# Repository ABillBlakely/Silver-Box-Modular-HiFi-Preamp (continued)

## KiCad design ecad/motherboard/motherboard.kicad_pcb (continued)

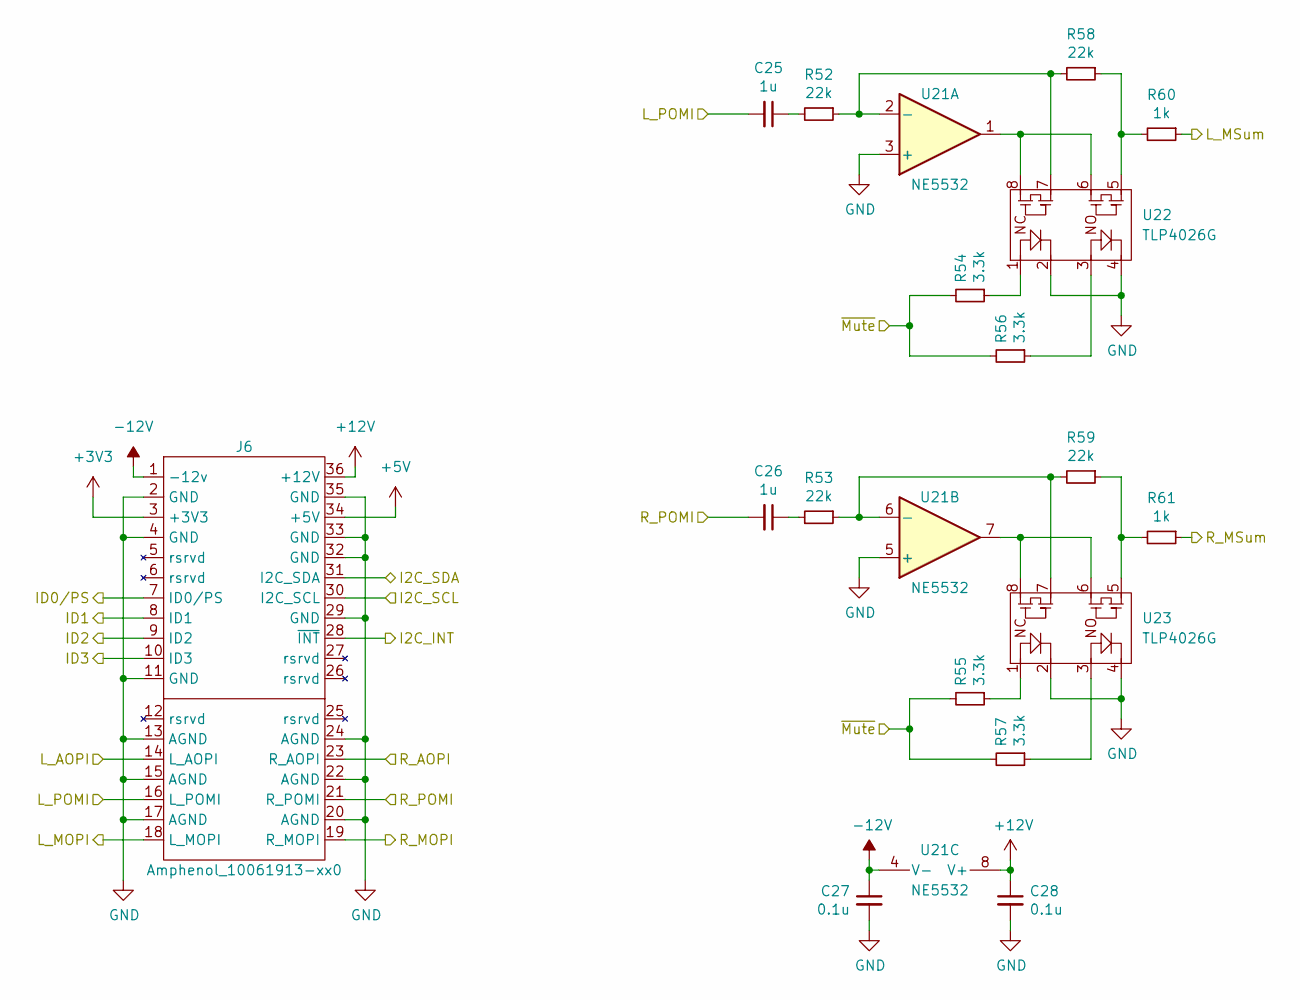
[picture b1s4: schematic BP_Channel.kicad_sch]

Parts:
C25, C26: 1u; C_2220_5650Metric_Pad1.97x5.40mm_HandSolder; MPN GRM55DR72E105KW01L
C27, C28: 0.1u; C_0603_1608Metric_Pad1.08x0.95mm_HandSolder; MPN C0603C104M5RACTU
J6: Amphenol_10061913-xx0; Card Edge Conn Amphenol 10061913-100PLF; MPN 10061913-110PLF
R52, R53, R58, R59: 22k; R_0603_1608Metric_Pad0.98x0.95mm_HandSolder; MPN RT0603FRE0722KL
R54, R55, R56, R57: 3.3k; R_0603_1608Metric_Pad0.98x0.95mm_HandSolder; MPN RC0603FR-073K3L
R60, R61: 1k; R_0603_1608Metric_Pad0.98x0.95mm_HandSolder; MPN RT0603FRE071KL
U21: NE5532; NE5532 SOIC8; MPN NE5532ADR
U22, U23: TLP4026G; MPN CPC2317NTR

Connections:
+3V3: J6.3 (+3V3); also elsewhere on the board
+5V: J6.34 (+5V); also elsewhere on the board
+12V: C28.1, J6.36 (+12V), U21.8 (V+); also elsewhere on the board
-12V: C27.1, J6.1 (-12v), U21.4 (V-); also elsewhere on the board
/BP_4Board_Control_and_Connect1/L_MSum: R60.1; also elsewhere on the board
/BP_4Board_Control_and_Connect1/L_POMI_4: J6.14 (L_AOPI); also elsewhere on the board
/BP_4Board_Control_and_Connect1/R_MSum: R61.1; also elsewhere on the board
/BP_4Board_Control_and_Connect1/R_POMI_4: J6.23 (R_AOPI); also elsewhere on the board
/BP_4Board_Control_and_Connect2/Channel1/I2C_INT: J6.28 (~INT); also elsewhere on the board
/BP_4Board_Control_and_Connect2/Channel1/I2C_SCL: J6.30 (I2C_SCL); also elsewhere on the board
/BP_4Board_Control_and_Connect2/Channel1/I2C_SDA: J6.31 (I2C_SDA); also elsewhere on the board
/BP_4Board_Control_and_Connect2/Channel1/ID0/PS: J6.7 (ID0/PS); also elsewhere on the board
/BP_4Board_Control_and_Connect2/Channel1/ID1: J6.8 (ID1); also elsewhere on the board
/BP_4Board_Control_and_Connect2/Channel1/ID2: J6.9 (ID2); also elsewhere on the board
/BP_4Board_Control_and_Connect2/Channel1/ID3: J6.10 (ID3); also elsewhere on the board
/BP_4Board_Control_and_Connect2/L_POMI_1: C25.2, J6.16 (L_POMI); also elsewhere on the board
/BP_4Board_Control_and_Connect2/R_POMI_1: C26.2, J6.21 (R_POMI); also elsewhere on the board
/L_MOPI: J6.18 (L_MOPI); also elsewhere on the board
/R_MOPI: J6.19 (R_MOPI); also elsewhere on the board
/~Mute_CH5: R54.2, R55.2, R56.2, R57.2; also elsewhere on the board
GND: C27.2, C28.2, J6.2 (GND), J6.4 (GND), J6.11 (GND), J6.13 (AGND), J6.15 (AGND), J6.17 (AGND), J6.20 (AGND), J6.22 (AGND), J6.24 (AGND), J6.29 (GND), J6.32 (GND), J6.33 (GND), J6.35 (GND), U21.3 (+), U21.5 (+), U22.2, U22.4, U23.2, U23.4; also elsewhere on the board
unnamed: C25.1, R52.2
unnamed: C26.1, R53.2
unnamed: R54.1, U22.1
unnamed: R55.1, U23.1
unnamed: R56.1, U22.3
unnamed: R57.1, U23.3
unnamed: R58.1, R60.2, U22.5
unnamed: R59.1, R61.2, U23.5
unnamed: U21.1, U22.6, U22.8
unnamed: U21.7, U23.6, U23.8
unnamed: R52.1, R58.2, U21.2 (-), U22.7
unnamed: R53.1, R59.2, U21.6 (-), U23.7

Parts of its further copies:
C6, C7, C10, C11, C14, C15, C18, C19, C29, C30, C33, C34, C37, C38: 1u; C_2220_5650Metric_Pad1.97x5.40mm_HandSolder; MPN GRM55DR72E105KW01L
C8, C9, C12, C13, C16, C17, C20, C21, C31, C32, C35, C36, C39, C40: 0.1u; C_0603_1608Metric_Pad1.08x0.95mm_HandSolder; MPN C0603C104M5RACTU
J2, J3, J4, J5, J7, J8, J9: Amphenol_10061913-xx0; Card Edge Conn Amphenol 10061913-100PLF; MPN 10061913-110PLF
R8, R9, R14, R15, R18, R19, R24, R25, R28, R29, R34, R35, R38, R39, R44, R45, R62, R63, R68, R69, R72, R73, R78, R79, R82, R83, R88, R89: 22k; R_0603_1608Metric_Pad0.98x0.95mm_HandSolder; MPN RT0603FRE0722KL
R10, R11, R12, R13, R20, R21, R22, R23, R30, R31, R32, R33, R40, R41, R42, R43, R64, R65, R66, R67, R74, R75, R76, R77, R84, R85, R86, R87: 3.3k; R_0603_1608Metric_Pad0.98x0.95mm_HandSolder; MPN RC0603FR-073K3L
R16, R17, R26, R27, R36, R37, R46, R47, R70, R71, R80, R81, R90, R91: 1k; R_0603_1608Metric_Pad0.98x0.95mm_HandSolder; MPN RT0603FRE071KL
U6, U9, U12, U15, U24, U27, U30: NE5532; NE5532 SOIC8; MPN NE5532ADR
U7, U8, U10, U11, U13, U14, U16, U17, U25, U26, U28, U29, U31, U32: TLP4026G; MPN CPC2317NTR

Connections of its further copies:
+3V3: J2.3 (+3V3), J3.3 (+3V3), J4.3 (+3V3), J5.3 (+3V3), J7.3 (+3V3), J8.3 (+3V3), J9.3 (+3V3); also elsewhere on the board
+5V: J2.34 (+5V), J3.34 (+5V), J4.34 (+5V), J5.34 (+5V), J7.34 (+5V), J8.34 (+5V), J9.34 (+5V); also elsewhere on the board
+12V: C9.1, C13.1, C17.1, C21.1, C32.1, C36.1, C40.1, J2.36 (+12V), J3.36 (+12V), J4.36 (+12V), J5.36 (+12V), J7.36 (+12V), J8.36 (+12V), J9.36 (+12V), U6.8 (V+), U9.8 (V+), U12.8 (V+), U15.8 (V+), U24.8 (V+), U27.8 (V+), U30.8 (V+); also elsewhere on the board
-12V: C8.1, C12.1, C16.1, C20.1, C31.1, C35.1, C39.1, J2.1 (-12v), J3.1 (-12v), J4.1 (-12v), J5.1 (-12v), J7.1 (-12v), J8.1 (-12v), J9.1 (-12v), U6.4 (V-), U9.4 (V-), U12.4 (V-), U15.4 (V-), U24.4 (V-), U27.4 (V-), U30.4 (V-); also elsewhere on the board
/BP_4Board_Control_and_Connect1/Channel1/I2C_INT: J2.28 (~INT); also elsewhere on the board
/BP_4Board_Control_and_Connect1/Channel1/I2C_SCL: J2.30 (I2C_SCL); also elsewhere on the board
/BP_4Board_Control_and_Connect1/Channel1/I2C_SDA: J2.31 (I2C_SDA); also elsewhere on the board
/BP_4Board_Control_and_Connect1/Channel1/ID0/PS: J2.7 (ID0/PS); also elsewhere on the board
/BP_4Board_Control_and_Connect1/Channel1/ID1: J2.8 (ID1); also elsewhere on the board
/BP_4Board_Control_and_Connect1/Channel1/ID2: J2.9 (ID2); also elsewhere on the board
/BP_4Board_Control_and_Connect1/Channel1/ID3: J2.10 (ID3); also elsewhere on the board
/BP_4Board_Control_and_Connect1/Channel2/I2C_INT: J3.28 (~INT); also elsewhere on the board
/BP_4Board_Control_and_Connect1/Channel2/I2C_SCL: J3.30 (I2C_SCL); also elsewhere on the board
/BP_4Board_Control_and_Connect1/Channel2/I2C_SDA: J3.31 (I2C_SDA); also elsewhere on the board
/BP_4Board_Control_and_Connect1/Channel2/ID0/PS: J3.7 (ID0/PS); also elsewhere on the board
/BP_4Board_Control_and_Connect1/Channel2/ID1: J3.8 (ID1); also elsewhere on the board
/BP_4Board_Control_and_Connect1/Channel2/ID2: J3.9 (ID2); also elsewhere on the board
/BP_4Board_Control_and_Connect1/Channel2/ID3: J3.10 (ID3); also elsewhere on the board
/BP_4Board_Control_and_Connect1/Channel3/I2C_INT: J4.28 (~INT); also elsewhere on the board
/BP_4Board_Control_and_Connect1/Channel3/I2C_SCL: J4.30 (I2C_SCL); also elsewhere on the board
/BP_4Board_Control_and_Connect1/Channel3/I2C_SDA: J4.31 (I2C_SDA); also elsewhere on the board
/BP_4Board_Control_and_Connect1/Channel3/ID0/PS: J4.7 (ID0/PS); also elsewhere on the board
/BP_4Board_Control_and_Connect1/Channel3/ID1: J4.8 (ID1); also elsewhere on the board
/BP_4Board_Control_and_Connect1/Channel3/ID2: J4.9 (ID2); also elsewhere on the board
/BP_4Board_Control_and_Connect1/Channel3/ID3: J4.10 (ID3); also elsewhere on the board
/BP_4Board_Control_and_Connect1/Channel4/I2C_INT: J5.28 (~INT); also elsewhere on the board
/BP_4Board_Control_and_Connect1/Channel4/I2C_SCL: J5.30 (I2C_SCL); also elsewhere on the board
/BP_4Board_Control_and_Connect1/Channel4/I2C_SDA: J5.31 (I2C_SDA); also elsewhere on the board
/BP_4Board_Control_and_Connect1/Channel4/ID0/PS: J5.7 (ID0/PS); also elsewhere on the board
/BP_4Board_Control_and_Connect1/Channel4/ID1: J5.8 (ID1); also elsewhere on the board
/BP_4Board_Control_and_Connect1/Channel4/ID2: J5.9 (ID2); also elsewhere on the board
/BP_4Board_Control_and_Connect1/Channel4/ID3: J5.10 (ID3); also elsewhere on the board
/BP_4Board_Control_and_Connect1/L_AOPI_1: J2.14 (L_AOPI)
/BP_4Board_Control_and_Connect1/L_MSum: R16.1, R26.1, R36.1, R46.1, R70.1, R80.1, R90.1; also elsewhere on the board
/BP_4Board_Control_and_Connect1/L_POMI_1: C6.2, J2.16 (L_POMI), J3.14 (L_AOPI)
/BP_4Board_Control_and_Connect1/L_POMI_2: C10.2, J3.16 (L_POMI), J4.14 (L_AOPI)
/BP_4Board_Control_and_Connect1/L_POMI_3: C14.2, J4.16 (L_POMI), J5.14 (L_AOPI)
/BP_4Board_Control_and_Connect1/L_POMI_4: C18.2, J5.16 (L_POMI); also elsewhere on the board
/BP_4Board_Control_and_Connect1/R_AOPI_1: J2.23 (R_AOPI)
/BP_4Board_Control_and_Connect1/R_MSum: R17.1, R27.1, R37.1, R47.1, R71.1, R81.1, R91.1; also elsewhere on the board
/BP_4Board_Control_and_Connect1/R_POMI_1: C7.2, J2.21 (R_POMI), J3.23 (R_AOPI)
/BP_4Board_Control_and_Connect1/R_POMI_2: C11.2, J3.21 (R_POMI), J4.23 (R_AOPI)
/BP_4Board_Control_and_Connect1/R_POMI_3: C15.2, J4.21 (R_POMI), J5.23 (R_AOPI)
/BP_4Board_Control_and_Connect1/R_POMI_4: C19.2, J5.21 (R_POMI); also elsewhere on the board
/BP_4Board_Control_and_Connect2/Channel2/I2C_INT: J7.28 (~INT); also elsewhere on the board
/BP_4Board_Control_and_Connect2/Channel2/I2C_SCL: J7.30 (I2C_SCL); also elsewhere on the board
/BP_4Board_Control_and_Connect2/Channel2/I2C_SDA: J7.31 (I2C_SDA); also elsewhere on the board
/BP_4Board_Control_and_Connect2/Channel2/ID0/PS: J7.7 (ID0/PS); also elsewhere on the board
/BP_4Board_Control_and_Connect2/Channel2/ID1: J7.8 (ID1); also elsewhere on the board
/BP_4Board_Control_and_Connect2/Channel2/ID2: J7.9 (ID2); also elsewhere on the board
/BP_4Board_Control_and_Connect2/Channel2/ID3: J7.10 (ID3); also elsewhere on the board
/BP_4Board_Control_and_Connect2/Channel3/I2C_INT: J8.28 (~INT); also elsewhere on the board
/BP_4Board_Control_and_Connect2/Channel3/I2C_SCL: J8.30 (I2C_SCL); also elsewhere on the board
/BP_4Board_Control_and_Connect2/Channel3/I2C_SDA: J8.31 (I2C_SDA); also elsewhere on the board
/BP_4Board_Control_and_Connect2/Channel3/ID0/PS: J8.7 (ID0/PS); also elsewhere on the board
/BP_4Board_Control_and_Connect2/Channel3/ID1: J8.8 (ID1); also elsewhere on the board
/BP_4Board_Control_and_Connect2/Channel3/ID2: J8.9 (ID2); also elsewhere on the board
/BP_4Board_Control_and_Connect2/Channel3/ID3: J8.10 (ID3); also elsewhere on the board
/BP_4Board_Control_and_Connect2/Channel4/I2C_INT: J9.28 (~INT); also elsewhere on the board
/BP_4Board_Control_and_Connect2/Channel4/I2C_SCL: J9.30 (I2C_SCL); also elsewhere on the board
/BP_4Board_Control_and_Connect2/Channel4/I2C_SDA: J9.31 (I2C_SDA); also elsewhere on the board
/BP_4Board_Control_and_Connect2/Channel4/ID0/PS: J9.7 (ID0/PS); also elsewhere on the board
/BP_4Board_Control_and_Connect2/Channel4/ID1: J9.8 (ID1); also elsewhere on the board
/BP_4Board_Control_and_Connect2/Channel4/ID2: J9.9 (ID2); also elsewhere on the board
/BP_4Board_Control_and_Connect2/Channel4/ID3: J9.10 (ID3); also elsewhere on the board
/BP_4Board_Control_and_Connect2/L_POMI_1: J7.14 (L_AOPI); also elsewhere on the board
/BP_4Board_Control_and_Connect2/L_POMI_2: C29.2, J7.16 (L_POMI), J8.14 (L_AOPI)
/BP_4Board_Control_and_Connect2/L_POMI_3: C33.2, J8.16 (L_POMI), J9.14 (L_AOPI)
/BP_4Board_Control_and_Connect2/L_POMI_4: C37.2, J9.16 (L_POMI)
/BP_4Board_Control_and_Connect2/R_POMI_1: J7.23 (R_AOPI); also elsewhere on the board
/BP_4Board_Control_and_Connect2/R_POMI_2: C30.2, J7.21 (R_POMI), J8.23 (R_AOPI)
/BP_4Board_Control_and_Connect2/R_POMI_3: C34.2, J8.21 (R_POMI), J9.23 (R_AOPI)
/BP_4Board_Control_and_Connect2/R_POMI_4: C38.2, J9.21 (R_POMI)
/L_MOPI: J2.18 (L_MOPI), J3.18 (L_MOPI), J4.18 (L_MOPI), J5.18 (L_MOPI), J7.18 (L_MOPI), J8.18 (L_MOPI), J9.18 (L_MOPI); also elsewhere on the board
/R_MOPI: J2.19 (R_MOPI), J3.19 (R_MOPI), J4.19 (R_MOPI), J5.19 (R_MOPI), J7.19 (R_MOPI), J8.19 (R_MOPI), J9.19 (R_MOPI); also elsewhere on the board
/~Mute_CH1: R10.2, R11.2, R12.2, R13.2; also elsewhere on the board
/~Mute_CH2: R20.2, R21.2, R22.2, R23.2; also elsewhere on the board
/~Mute_CH3: R30.2, R31.2, R32.2, R33.2; also elsewhere on the board
/~Mute_CH4: R40.2, R41.2, R42.2, R43.2; also elsewhere on the board
/~Mute_CH6: R64.2, R65.2, R66.2, R67.2; also elsewhere on the board
/~Mute_CH7: R74.2, R75.2, R76.2, R77.2; also elsewhere on the board
/~Mute_CH8: R84.2, R85.2, R86.2, R87.2; also elsewhere on the board
GND: C8.2, C9.2, C12.2, C13.2, C16.2, C17.2, C20.2, C21.2, C31.2, C32.2, C35.2, C36.2, C39.2, C40.2, J2.2 (GND), J2.4 (GND), J2.11 (GND), J2.13 (AGND), J2.15 (AGND), J2.17 (AGND), J2.20 (AGND), J2.22 (AGND), J2.24 (AGND), J2.29 (GND), J2.32 (GND), J2.33 (GND), J2.35 (GND), J3.2 (GND), J3.4 (GND), J3.11 (GND), J3.13 (AGND), J3.15 (AGND), J3.17 (AGND), J3.20 (AGND), J3.22 (AGND), J3.24 (AGND), J3.29 (GND), J3.32 (GND), J3.33 (GND), J3.35 (GND), J4.2 (GND), J4.4 (GND), J4.11 (GND), J4.13 (AGND), J4.15 (AGND), J4.17 (AGND), J4.20 (AGND), J4.22 (AGND), J4.24 (AGND), J4.29 (GND), J4.32 (GND), J4.33 (GND), J4.35 (GND), J5.2 (GND), J5.4 (GND), J5.11 (GND), J5.13 (AGND), J5.15 (AGND), J5.17 (AGND), J5.20 (AGND), J5.22 (AGND), J5.24 (AGND), J5.29 (GND), J5.32 (GND), J5.33 (GND), J5.35 (GND), J7.2 (GND), J7.4 (GND), J7.11 (GND), J7.13 (AGND), J7.15 (AGND), J7.17 (AGND), J7.20 (AGND), J7.22 (AGND), J7.24 (AGND), J7.29 (GND), J7.32 (GND), J7.33 (GND), J7.35 (GND), J8.2 (GND), J8.4 (GND), J8.11 (GND), J8.13 (AGND), J8.15 (AGND), J8.17 (AGND), J8.20 (AGND), J8.22 (AGND), J8.24 (AGND), J8.29 (GND), J8.32 (GND), J8.33 (GND), J8.35 (GND), J9.2 (GND), J9.4 (GND), J9.11 (GND), J9.13 (AGND), J9.15 (AGND), J9.17 (AGND), J9.20 (AGND), J9.22 (AGND), J9.24 (AGND), J9.29 (GND), J9.32 (GND), J9.33 (GND), J9.35 (GND), U6.3 (+), U6.5 (+), U7.2, U7.4, U8.2, U8.4, U9.3 (+), U9.5 (+), U10.2, U10.4, U11.2, U11.4, U12.3 (+), U12.5 (+), U13.2, U13.4, U14.2, U14.4, U15.3 (+), U15.5 (+), U16.2, U16.4, U17.2, U17.4, U24.3 (+), U24.5 (+), U25.2, U25.4, U26.2, U26.4, U27.3 (+), U27.5 (+), U28.2, U28.4, U29.2, U29.4, U30.3 (+), U30.5 (+), U31.2, U31.4, U32.2, U32.4; also elsewhere on the board
unnamed: C6.1, R8.2
unnamed: C7.1, R9.2
unnamed: C10.1, R18.2
unnamed: C11.1, R19.2
unnamed: C14.1, R28.2
unnamed: C15.1, R29.2
unnamed: C18.1, R38.2
unnamed: C19.1, R39.2
unnamed: C29.1, R62.2
unnamed: C30.1, R63.2
unnamed: C33.1, R72.2
unnamed: C34.1, R73.2
unnamed: C37.1, R82.2
unnamed: C38.1, R83.2
unnamed: R10.1, U7.1
unnamed: R11.1, U8.1
unnamed: R12.1, U7.3
unnamed: R13.1, U8.3
unnamed: R14.1, R16.2, U7.5
unnamed: R15.1, R17.2, U8.5
unnamed: R20.1, U10.1
unnamed: R21.1, U11.1
unnamed: R22.1, U10.3
unnamed: R23.1, U11.3
unnamed: R24.1, R26.2, U10.5
unnamed: R25.1, R27.2, U11.5
unnamed: R30.1, U13.1
unnamed: R31.1, U14.1
unnamed: R32.1, U13.3
unnamed: R33.1, U14.3
unnamed: R34.1, R36.2, U13.5
unnamed: R35.1, R37.2, U14.5
unnamed: R40.1, U16.1
unnamed: R41.1, U17.1
unnamed: R42.1, U16.3
unnamed: R43.1, U17.3
unnamed: R44.1, R46.2, U16.5
unnamed: R45.1, R47.2, U17.5
unnamed: R64.1, U25.1
unnamed: R65.1, U26.1
unnamed: R66.1, U25.3
unnamed: R67.1, U26.3
unnamed: R68.1, R70.2, U25.5
unnamed: R69.1, R71.2, U26.5
unnamed: R74.1, U28.1
unnamed: R75.1, U29.1
unnamed: R76.1, U28.3
unnamed: R77.1, U29.3
unnamed: R78.1, R80.2, U28.5
unnamed: R79.1, R81.2, U29.5
unnamed: R84.1, U31.1
unnamed: R85.1, U32.1
unnamed: R86.1, U31.3
unnamed: R87.1, U32.3
unnamed: R88.1, R90.2, U31.5
unnamed: R89.1, R91.2, U32.5
unnamed: U6.1, U7.6, U7.8
unnamed: U6.7, U8.6, U8.8
unnamed: R8.1, R14.2, U6.2 (-), U7.7
unnamed: R9.1, R15.2, U6.6 (-), U8.7
unnamed: R18.1, R24.2, U9.2 (-), U10.7
unnamed: R19.1, R25.2, U9.6 (-), U11.7
unnamed: U9.1, U10.6, U10.8
unnamed: U9.7, U11.6, U11.8
unnamed: U12.1, U13.6, U13.8
unnamed: U12.7, U14.6, U14.8
unnamed: R28.1, R34.2, U12.2 (-), U13.7
unnamed: R29.1, R35.2, U12.6 (-), U14.7
unnamed: U15.1, U16.6, U16.8
unnamed: U15.7, U17.6, U17.8
unnamed: R38.1, R44.2, U15.2 (-), U16.7
unnamed: R39.1, R45.2, U15.6 (-), U17.7
unnamed: U24.1, U25.6, U25.8
unnamed: U24.7, U26.6, U26.8
unnamed: R62.1, R68.2, U24.2 (-), U25.7
unnamed: R63.1, R69.2, U24.6 (-), U26.7
unnamed: U27.1, U28.6, U28.8
unnamed: U27.7, U29.6, U29.8
unnamed: R72.1, R78.2, U27.2 (-), U28.7
unnamed: R73.1, R79.2, U27.6 (-), U29.7
unnamed: U30.1, U31.6, U31.8
unnamed: U30.7, U32.6, U32.8
unnamed: R82.1, R88.2, U30.2 (-), U31.7
unnamed: R83.1, R89.2, U30.6 (-), U32.7

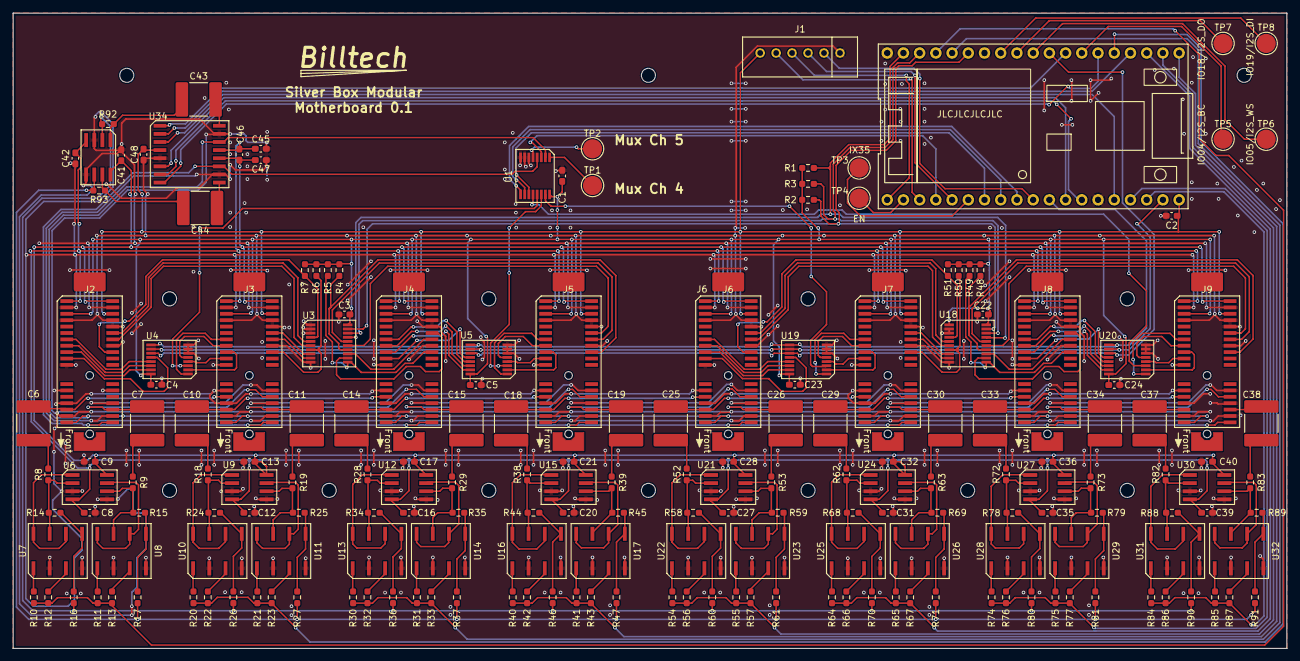
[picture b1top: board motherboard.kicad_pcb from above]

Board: 2 copper layers, 199.5 x 99.5 mm, 192 parts (0 on the bottom side), 221 nets.

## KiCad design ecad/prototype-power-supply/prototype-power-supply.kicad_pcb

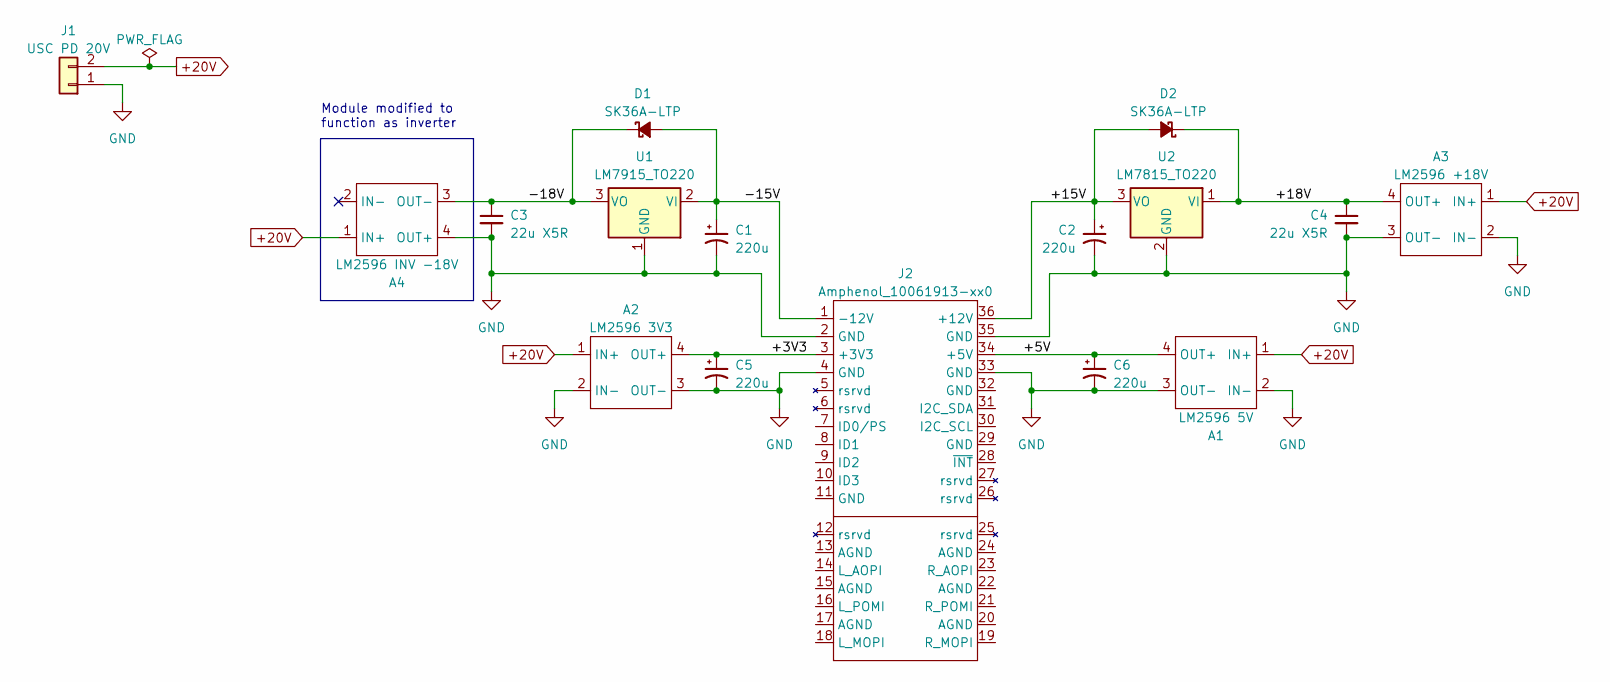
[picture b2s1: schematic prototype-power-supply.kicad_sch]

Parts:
A1: LM2596 5V; LM2596 module
A2: LM2596 3V3; LM2596 module
A3: LM2596 +18V; LM2596 module
A4: LM2596 INV -18V; LM2596 module
C1, C2, C5, C6: 220u; CP_Elec_12.5x13.5
C3, C4: 22u X5R; C_1210_3225Metric
D1, D2: SK36A-LTP; D_SMA_Handsoldering
J1: USC PD 20V; JST_XH_B2B-XH-A_1x02_P2.50mm_Vertical
J2: Amphenol_10061913-xx0; Card Edge board Amphenol 10061913-100PLF
U1: LM7915_TO220; TO-220-3_Vertical
U2: LM7815_TO220; TO-220-3_Vertical

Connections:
+20V: A1.1 (IN+), A2.1 (IN+), A3.1 (IN+), A4.1 (IN+), J1.2
/+3V3: A2.4 (OUT+), C5.1, J2.3 (+3V3)
/+5V: A1.4 (OUT+), C6.1, J2.34 (+5V)
/+15V: C2.1, D2.2 (A), J2.36 (+12V), U2.3 (VO)
/+18V: A3.4 (OUT+), C4.1, D2.1 (K), U2.1 (VI)
/-15V: C1.1, D1.2 (A), J2.1 (-12V), U1.2 (VI)
/-18V: A4.3 (OUT-), C3.1, D1.1 (K), U1.3 (VO)
GND: A1.2 (IN-), A1.3 (OUT-), A2.2 (IN-), A2.3 (OUT-), A3.2 (IN-), A3.3 (OUT-), A4.4 (OUT+), C1.2, C2.2, C3.2, C4.2, C5.2, C6.2, J1.1, J2.2 (GND), J2.4 (GND), J2.33 (GND), J2.35 (GND), U1.1 (GND), U2.2 (GND)

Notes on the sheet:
Module modified to function as inverter

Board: 2 copper layers, 16 parts (2 on the bottom side), 8 nets, no tracks yet.

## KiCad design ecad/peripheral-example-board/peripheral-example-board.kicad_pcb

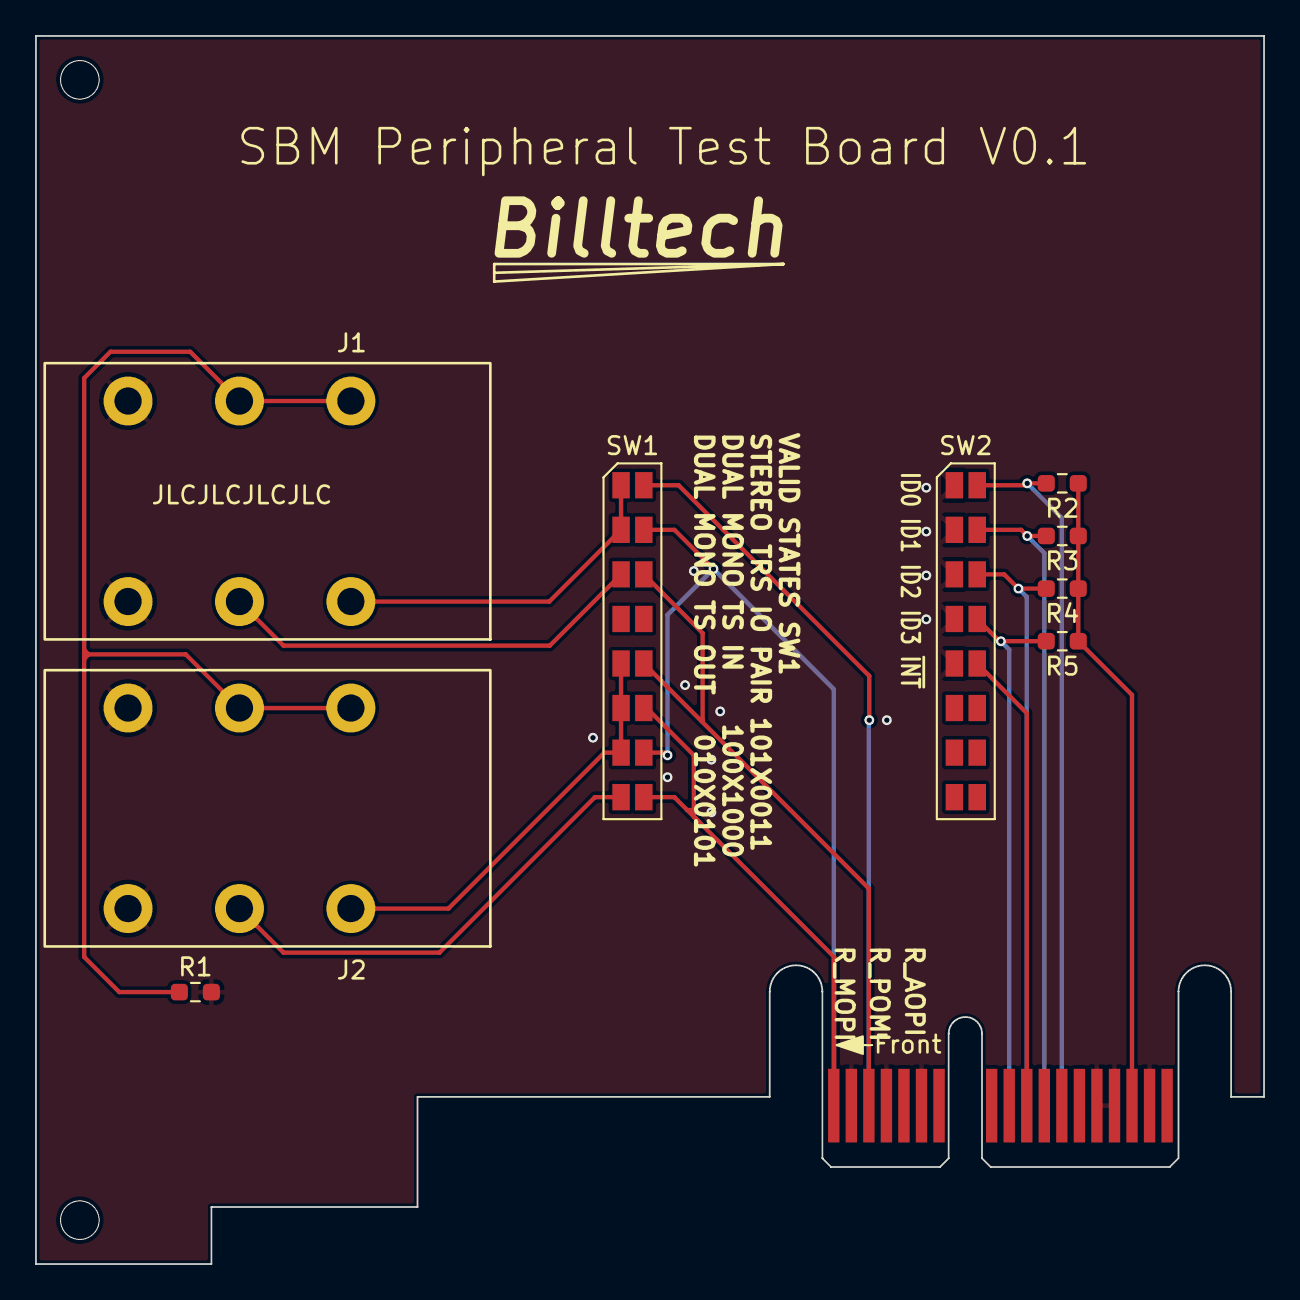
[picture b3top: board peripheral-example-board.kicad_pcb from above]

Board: 2 copper layers, 70.0 x 70.0 mm, 11 parts (0 on the bottom side), 16 nets.

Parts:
J1, J2: Amphenol_ACJS-MHOM; ACJS-MHOM
LOGO: Billtech
P1: Amphenol_10061913-xx0; Card Edge board Amphenol 10061913-100PLF
R1, R2, R3, R4, R5: 10k; R_0603_1608Metric_Pad0.98x0.95mm_HandSolder
SW1, SW2: SW_DIP_x08; 1x8 solder bridge 1x1.5x0.3

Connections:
/+5V: P1.34 (+5V), R2.1, R3.1, R4.1, R5.1
/ID0: P1.7 (ID0/PS), R2.2, SW2.16
/ID1: P1.8 (ID1), R3.2, SW2.15
/ID2: P1.9 (ID2), R4.2, SW2.14
/ID3: P1.10 (ID3), R5.2, SW2.13
/L_MOPI: P1.18 (L_MOPI), SW1.10, SW1.15
/L_POMI: P1.16 (L_POMI), SW1.16
/R1: J1.R, SW1.3
/R2: J2.R, SW1.8
/R_MOPI: P1.19 (R_MOPI), SW1.9, SW1.11
/R_POMI: P1.21 (R_POMI), SW1.12, SW1.14
/T1: J1.T, SW1.1, SW1.2
/T2: J2.T, SW1.5, SW1.6, SW1.7
/~INT: P1.28 (~INT), SW2.12
GND: J1.S, J1.SN, J2.S, J2.SN, P1.2 (GND), P1.4 (GND), P1.11 (GND), P1.13 (AGND), P1.15 (AGND), P1.17 (AGND), P1.20 (AGND), P1.22 (AGND), P1.24 (AGND), P1.29 (GND), P1.32 (GND), P1.33 (GND), P1.35 (GND), R1.2, SW2.1, SW2.2, SW2.3, SW2.4, SW2.5
unnamed: J1.RN, J1.TN, J2.RN, J2.TN, R1.1

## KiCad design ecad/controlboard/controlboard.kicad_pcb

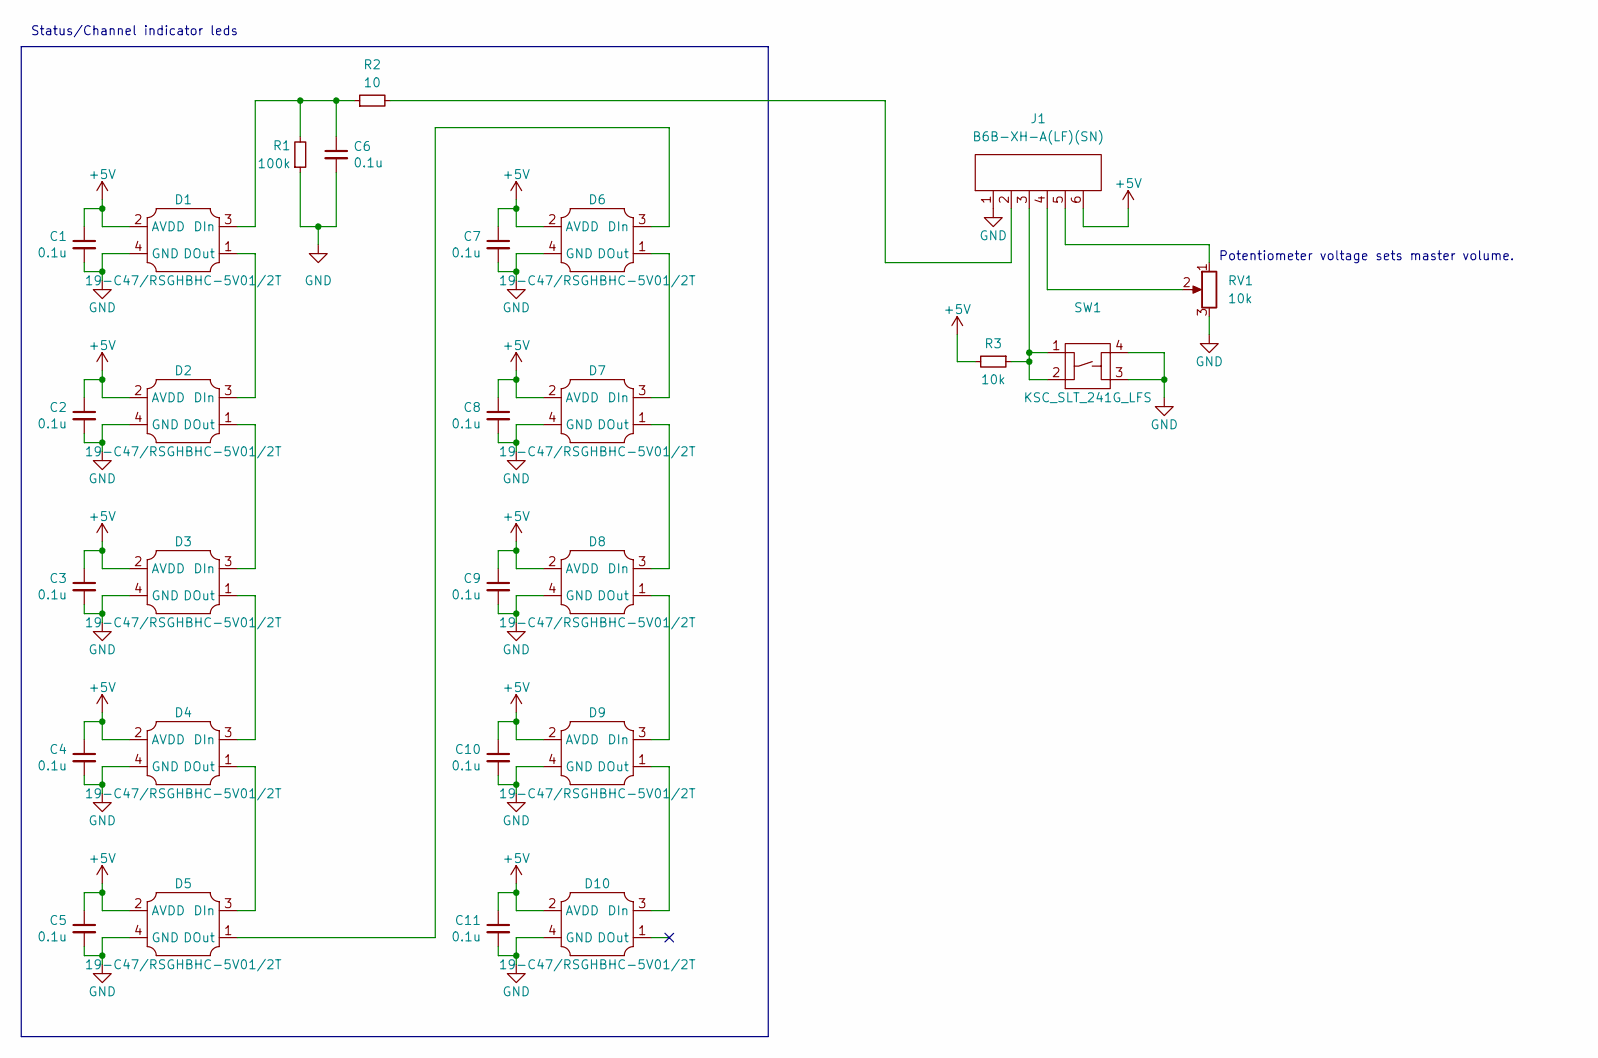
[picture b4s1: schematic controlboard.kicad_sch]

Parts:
C1, C2, C3, C4, C5, C6, C7, C8, C9, C10, C11: 0.1u; C_0603_1608Metric_Pad1.08x0.95mm_HandSolder
D1, D2, D3, D4, D5, D6, D7, D8, D9, D10: 19-C47/RSGHBHC-5V01/2T; 19-C47 RSGHBHC-5V01 2T
J1: B6B-XH-A(LF)(SN)
R1: 100k; R_0603_1608Metric_Pad0.98x0.95mm_HandSolder
R2: 10; R_0603_1608Metric_Pad0.98x0.95mm_HandSolder
R3: 10k; R_0603_1608Metric_Pad0.98x0.95mm_HandSolder
RV1: 10k; Bourns PTV11-4425A
SW1: KSC_SLT_241G_LFS; KSC SLT 241G LFS

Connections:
+5V: C1.1, C2.1, C3.1, C4.1, C5.1, C7.1, C8.1, C9.1, C10.1, C11.1, D1.2 (AVDD), D2.2 (AVDD), D3.2 (AVDD), D4.2 (AVDD), D5.2 (AVDD), D6.2 (AVDD), D7.2 (AVDD), D8.2 (AVDD), D9.2 (AVDD), D10.2 (AVDD), J1.6, R3.2
GND: C1.2, C2.2, C3.2, C4.2, C5.2, C6.2, C7.2, C8.2, C9.2, C10.2, C11.2, D1.4 (GND), D2.4 (GND), D3.4 (GND), D4.4 (GND), D5.4 (GND), D6.4 (GND), D7.4 (GND), D8.4 (GND), D9.4 (GND), D10.4 (GND), J1.1, R1.1, RV1.3, SW1.3, SW1.4
unnamed: C6.1, D1.3 (DIn), R1.2, R2.1
unnamed: D1.1 (DOut), D2.3 (DIn)
unnamed: D2.1 (DOut), D3.3 (DIn)
unnamed: D3.1 (DOut), D4.3 (DIn)
unnamed: D4.1 (DOut), D5.3 (DIn)
unnamed: D5.1 (DOut), D6.3 (DIn)
unnamed: D6.1 (DOut), D7.3 (DIn)
unnamed: D7.1 (DOut), D8.3 (DIn)
unnamed: D8.1 (DOut), D9.3 (DIn)
unnamed: D9.1 (DOut), D10.3 (DIn)
unnamed: J1.2, R2.2
unnamed: J1.3, R3.1, SW1.1, SW1.2
unnamed: J1.4, RV1.2
unnamed: J1.5, RV1.1

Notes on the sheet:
Status/Channel indicator leds
Potentiometer voltage sets master volume.

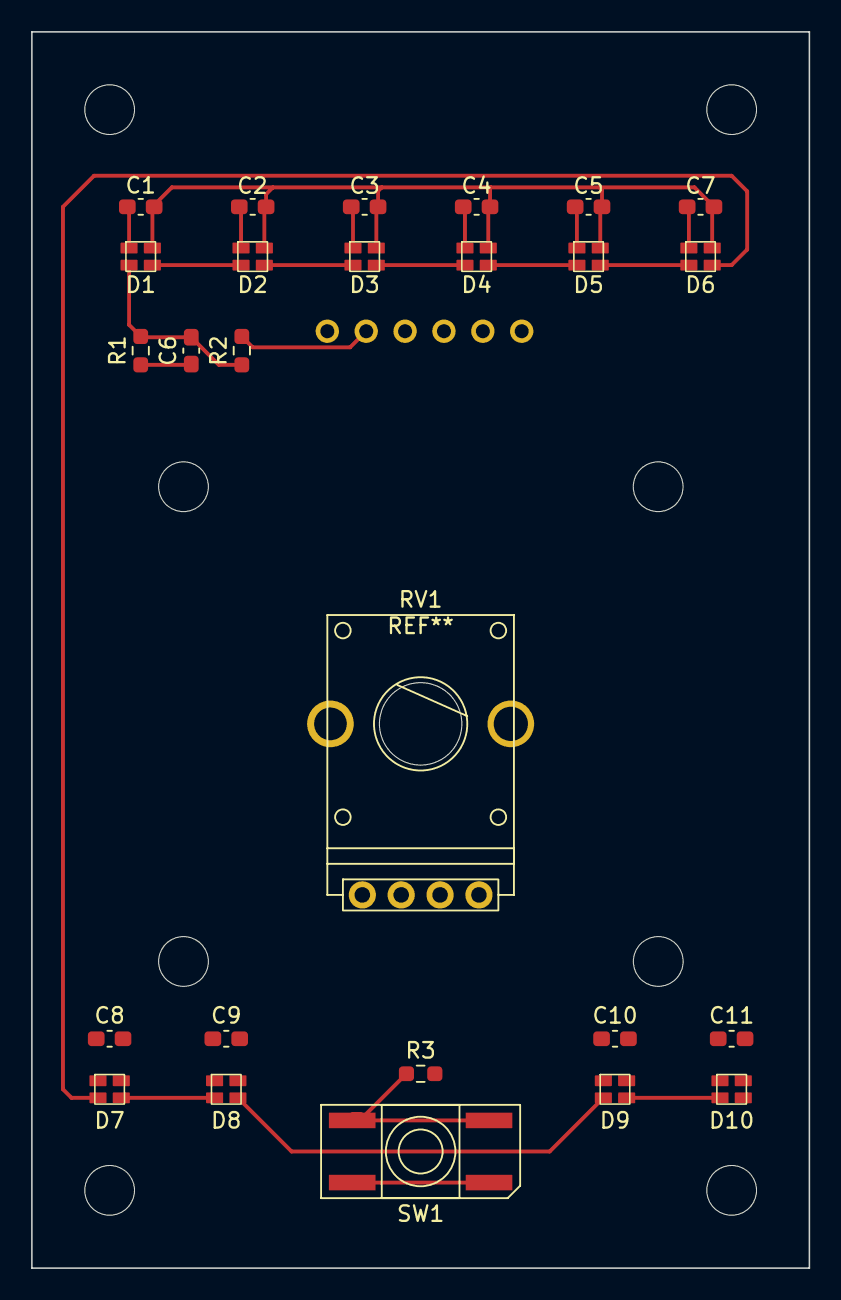
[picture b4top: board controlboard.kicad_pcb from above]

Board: 2 copper layers, 50.0 x 79.5 mm, 27 parts (1 on the bottom side), 16 nets.

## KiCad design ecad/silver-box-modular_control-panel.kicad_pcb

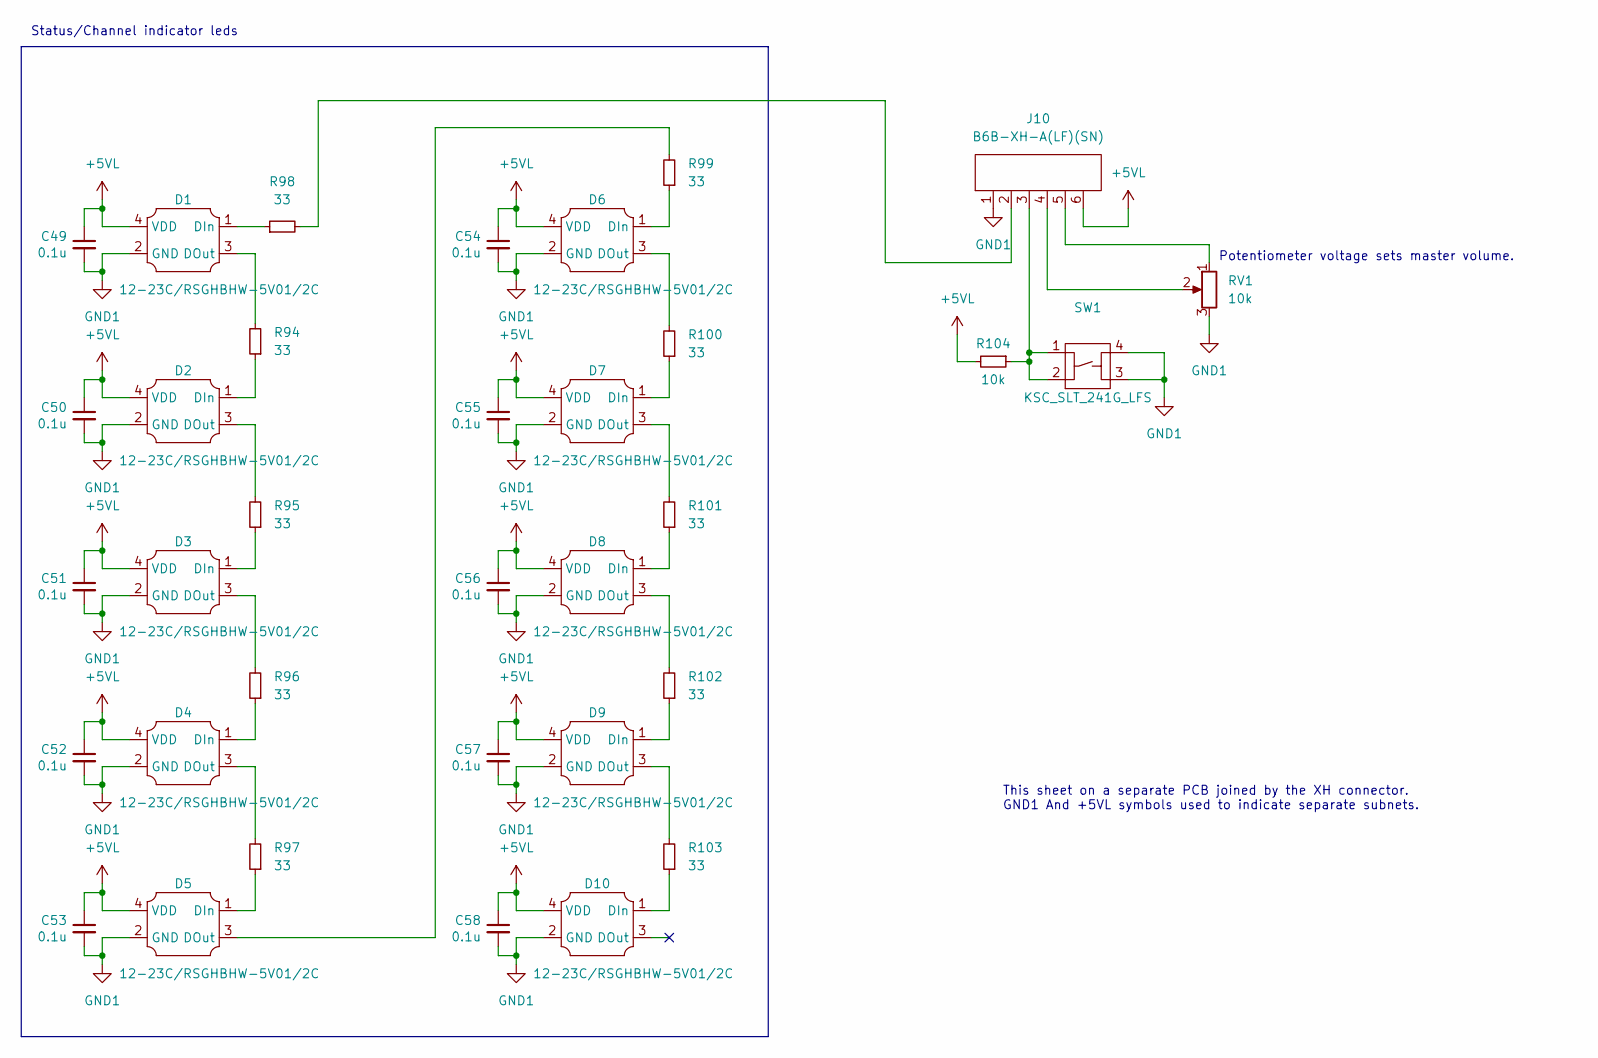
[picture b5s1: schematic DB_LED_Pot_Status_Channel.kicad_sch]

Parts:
C49, C50, C51, C52, C53, C54, C55, C56, C57, C58: 0.1u; C_0603_1608Metric_Pad1.08x0.95mm_HandSolder
D1, D2, D3, D4, D5, D6, D7, D8, D9, D10: 12-23C/RSGHBHW-5V01/2C; 12-23C-RSGHBHW-5V01-2C
J10: B6B-XH-A(LF)(SN)
R94, R95, R96, R97, R98, R99, R100, R101, R102, R103: 33; R_0603_1608Metric_Pad0.98x0.95mm_HandSolder
R104: 10k; R_0603_1608Metric_Pad0.98x0.95mm_HandSolder
RV1: 10k; Bourns PTV11-4425A
SW1: KSC_SLT_241G_LFS; KSC SLT 241G LFS

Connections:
+5VL: C49.1, C50.1, C51.1, C52.1, C53.1, C54.1, C55.1, C56.1, C57.1, C58.1, D1.4 (VDD), D2.4 (VDD), D3.4 (VDD), D4.4 (VDD), D5.4 (VDD), D6.4 (VDD), D7.4 (VDD), D8.4 (VDD), D9.4 (VDD), D10.4 (VDD), J10.6, R104.2
GND1: C49.2, C50.2, C51.2, C52.2, C53.2, C54.2, C55.2, C56.2, C57.2, C58.2, D1.2 (GND), D2.2 (GND), D3.2 (GND), D4.2 (GND), D5.2 (GND), D6.2 (GND), D7.2 (GND), D8.2 (GND), D9.2 (GND), D10.2 (GND), J10.1, RV1.3, SW1.3, SW1.4
unnamed: D1.1 (DIn), R98.1
unnamed: D1.3 (DOut), R94.2
unnamed: D2.1 (DIn), R94.1
unnamed: D2.3 (DOut), R95.2
unnamed: D3.1 (DIn), R95.1
unnamed: D3.3 (DOut), R96.2
unnamed: D4.1 (DIn), R96.1
unnamed: D4.3 (DOut), R97.2
unnamed: D5.1 (DIn), R97.1
unnamed: D5.3 (DOut), R99.2
unnamed: D6.1 (DIn), R99.1
unnamed: D6.3 (DOut), R100.2
unnamed: D7.1 (DIn), R100.1
unnamed: D7.3 (DOut), R101.2
unnamed: D8.1 (DIn), R101.1
unnamed: D8.3 (DOut), R102.2
unnamed: D9.1 (DIn), R102.1
unnamed: D9.3 (DOut), R103.2
unnamed: D10.1 (DIn), R103.1
unnamed: J10.2, R98.2
unnamed: J10.3, R104.1, SW1.1, SW1.2
unnamed: J10.4, RV1.2
unnamed: J10.5, RV1.1

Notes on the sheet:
Potentiometer voltage sets master volume.
Status/Channel indicator leds
This sheet on a separate PCB joined by the XH connector. GND1 And +5VL symbols used to indicate separate subnets.

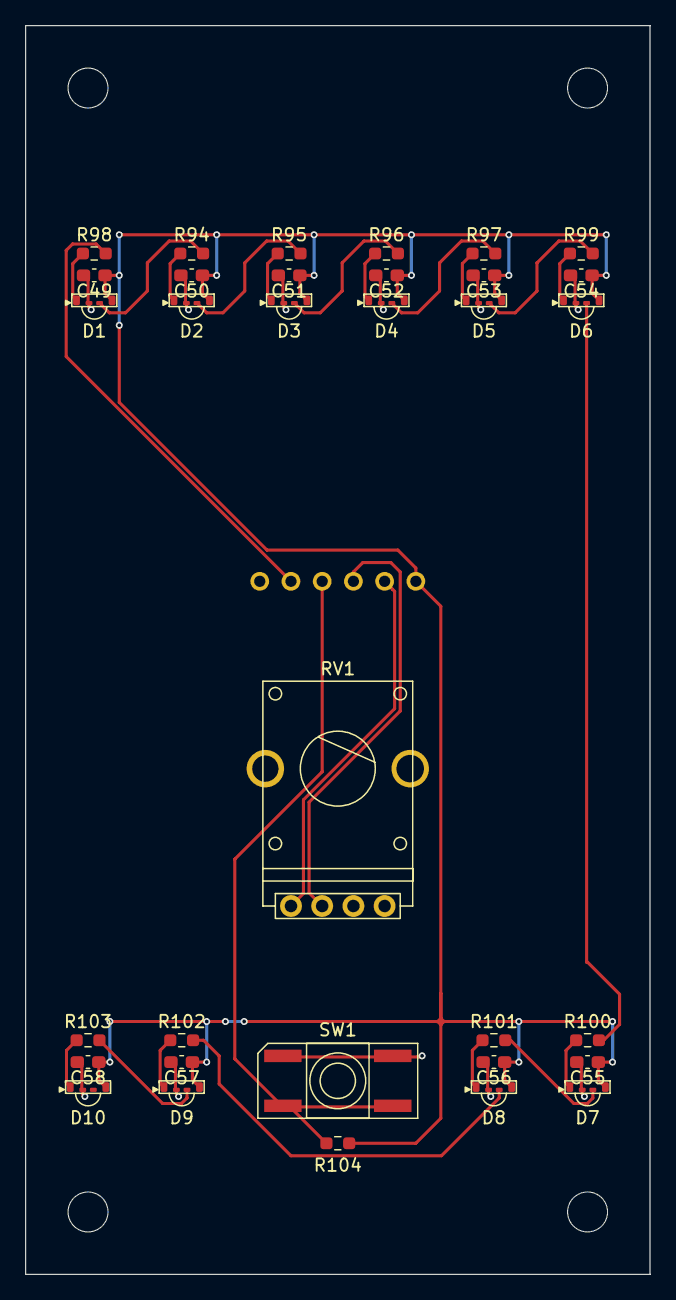
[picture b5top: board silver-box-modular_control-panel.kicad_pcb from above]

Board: 2 copper layers, 50.0 x 100.0 mm, 35 parts (1 on the bottom side), 25 nets.

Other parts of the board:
control_plate: Board
